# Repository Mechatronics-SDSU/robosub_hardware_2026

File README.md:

# robosub_hardware_2026

Repository for EDA and dependencies for RoboSub 2026 electrical hardware

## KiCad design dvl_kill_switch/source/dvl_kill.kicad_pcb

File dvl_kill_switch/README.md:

# DVL Kill Switch PCB

Hall-effect based kill switch PCB for the DVL sensor

## Overview

This board uses a hall-effect sensor to detect the presence of a magnet, allowing the DVL system to be enabled or disabled externally without physical electrical contact.

## Features

- Magnetic kill switch operation
- Hall-effect sensor based detection
- Compact PCB design
- Designed in KiCad

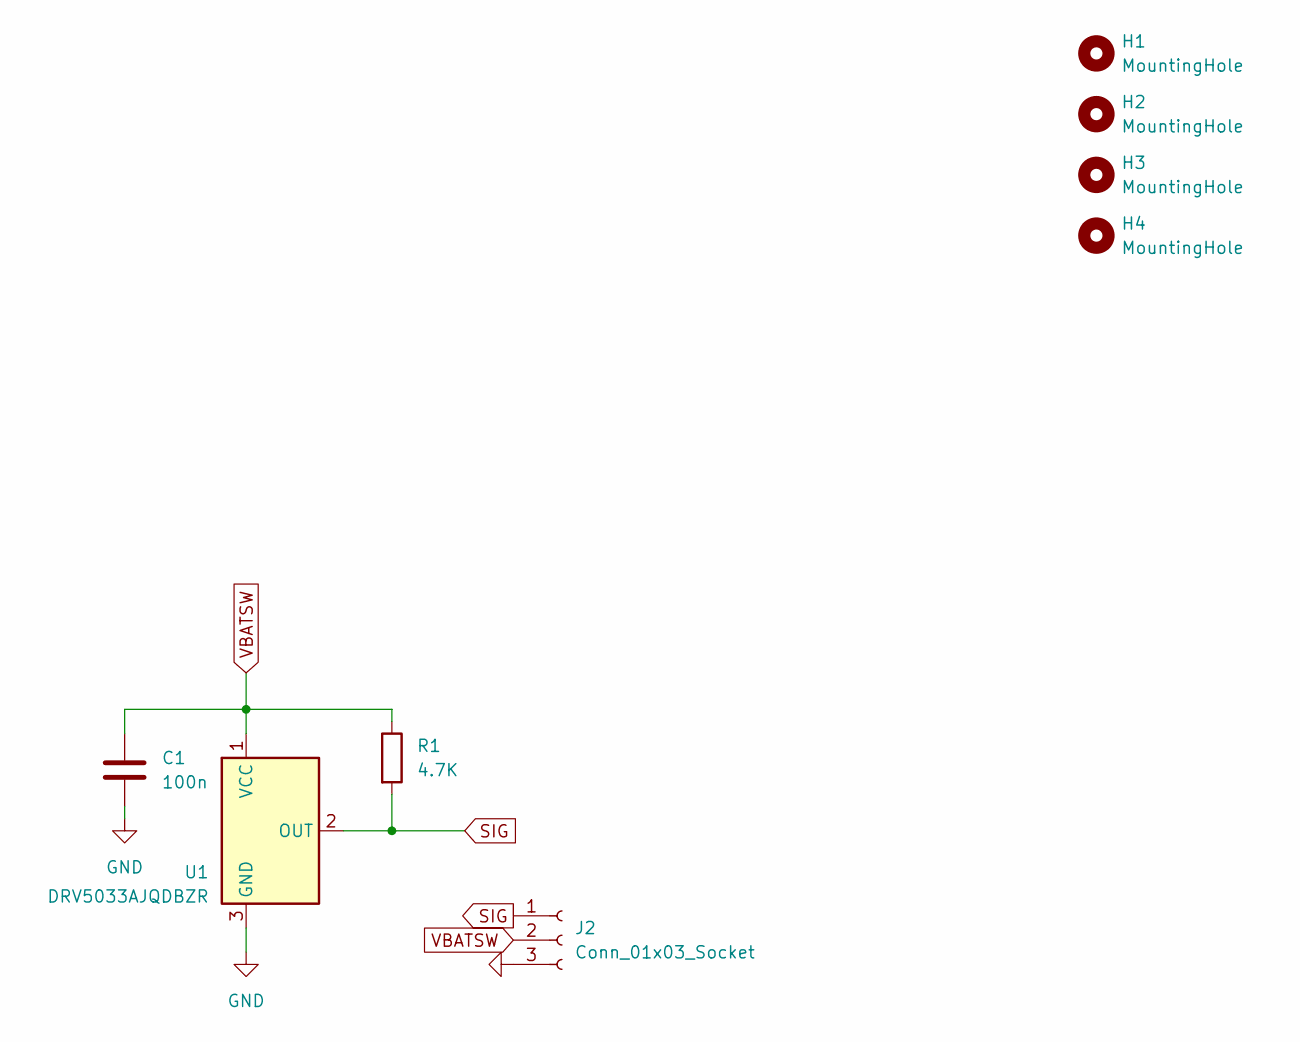
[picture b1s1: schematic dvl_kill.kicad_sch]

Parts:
C1: 100n; C_0805_2012Metric
H1, H2, H3, H4: MountingHole; MountingHole_2.2mm_M2
J2: Conn_01x03_Socket; SAMTEC_IPL1-103-01-X-S-RA-K
R1: 4.7K; R_0805_2012Metric
U1: DRV5033AJQDBZR; SOT-23

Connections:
GND: C1.2, J2.3, U1.3 (GND)
SIG: J2.1, R1.2, U1.2 (OUT)
VBATSW: C1.1, J2.2, R1.1, U1.1 (VCC)

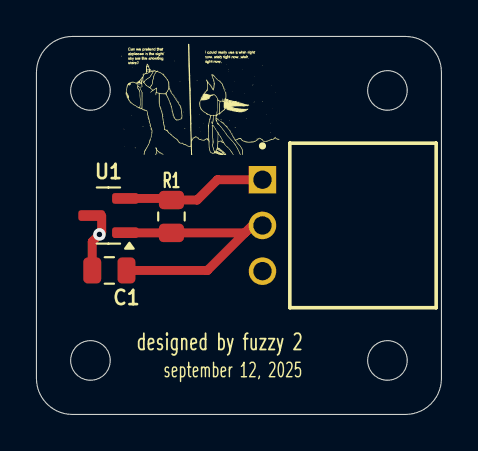
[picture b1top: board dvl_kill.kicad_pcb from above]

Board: 2 copper layers, 22.5 x 21.0 mm, 8 parts (0 on the bottom side), 3 nets.

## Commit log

2026-02-26 initial directories
2026-06-04 Add README for DVL Kill Switch PCB
2026-06-04 gerber files
2026-06-04 poop
2026-06-04 add gerber files
2026-06-04 poopoo
2026-06-04 .pretty files
2026-06-04 source files
2026-06-04 schematic upload
